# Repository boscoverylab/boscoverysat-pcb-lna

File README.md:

# Proyecto BoscoverySAT

### Descripción.

Este repositorio contiene el esquema electrónico así como el diseño de placa PCB para la implementación de un preamplificador LNB.

### Contenido del repositorio.

El presente repositorio está dividido en los siguientes directorios:

* [eagle](eagle/) - Contiene el proyecto donde se ha diseñado el esquema de circuito y se ha creado el PCB.
* [docs](docs/) - Contiene información adicional del proyecto como listado de componentes o fotolito del PCB.
* img - Esta carpeta contiene imágenes propias de la configuración del repositorio.

### Características del diseño.

El proyecto de esquema y placa PCB ha sido realizado mediante la aplicación [Cadsoft Eagle 6.5.0](http://www.cadsoftusa.com/download-eagle/).

### Contacto.

Para cualquier duda o contacto que desee realizar, por favor, remita un correo electrónico a la siguiente dirección: [boscoverylab@gmail.com](boscoverylab@gmail.com) y nos pondremos en contacto con usted a la mayor brevedad.

Si lo desea, también puede contactar con nosotros a través de nuestra cuenta de Twitter [@boscoverylab](https://www.twitter.com/boscoverylab).

### Licenciamiento.

Cualquier producto, marca comercial o nombre corporativo empleado en el contenido del presente repositorio, se ha usado con el objetivo de identificar y/o explicar conceptos, sin intención alguna de infringir los términos de uso y/o licencias de los mismos.

El presente documento se distribuye en cualquiera de sus formatos, bajo la licencia internacional [Reconocimiento-NoComercial-CompartirIgual 4.0 Internacional de Creative Commons](http://creativecommons.org/licenses/by-nc-sa/4.0/), no estando autorizada la reclamación de ningún derecho ni cantidad económica alguna en nombre de su autor o autores, a ninguna Entidad de Derechos de Autor, tanto española como internacional.

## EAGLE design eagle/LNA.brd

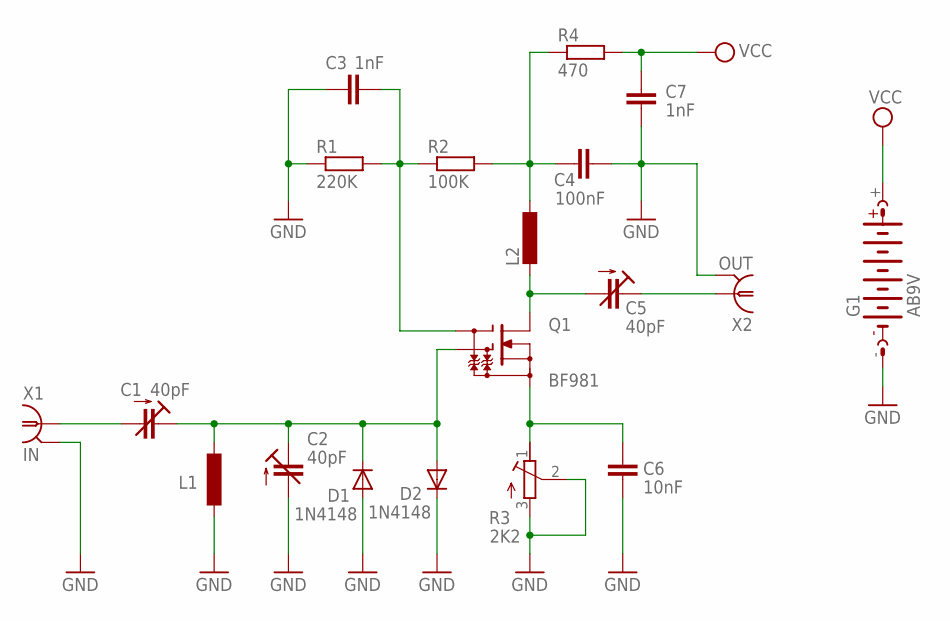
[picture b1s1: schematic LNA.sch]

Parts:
C1, C2, C5: 40pF; CTRIM808-BC
C3, C7: 1nF; C050-025X075
C4: 100nF; C050-025X075
C6: 10nF; C050-025X075
D1, D2: 1N4148; DO35-7
G1: AB9V
L1, L2: L-EU0204/5; 0204/5
Q1: BF981; SOT103
R1: 220K; 0207/10
R2: 100K; 0207/10
R3: 2K2; RTRIM43P
R4: 470; 0207/10
X1: IN; A1944
X2: OUT; A1944

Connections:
GND: C2.2 (A), C3.1, C4.2, C6.2, C7.2, D1.A, D2.C, G1.-, L1.2, R1.1, R3.2 (S), R3.3 (E), X1.2, X1.3 (2), X1.4 (2), X1.5 (2), X2.2, X2.3 (2), X2.4 (2), X2.5 (2)
unnamed: C4.1, L2.1, R2.2, R4.1
unnamed: C3.2, Q1.4-G1 (G1), R1.2, R2.1
unnamed: C1.1 (E), C2.1 (E), D1.C, D2.A, L1.1, Q1.3-G2 (G2)
unnamed: C5.2 (A), L2.2, Q1.2-D (DRAIN)
unnamed: C5.1 (E), X2.1
unnamed: C1.2 (A), X1.1
unnamed: C6.1, Q1.1-S (SOURCE), R3.1 (A)
VCC: C7.1, G1.+, R4.2

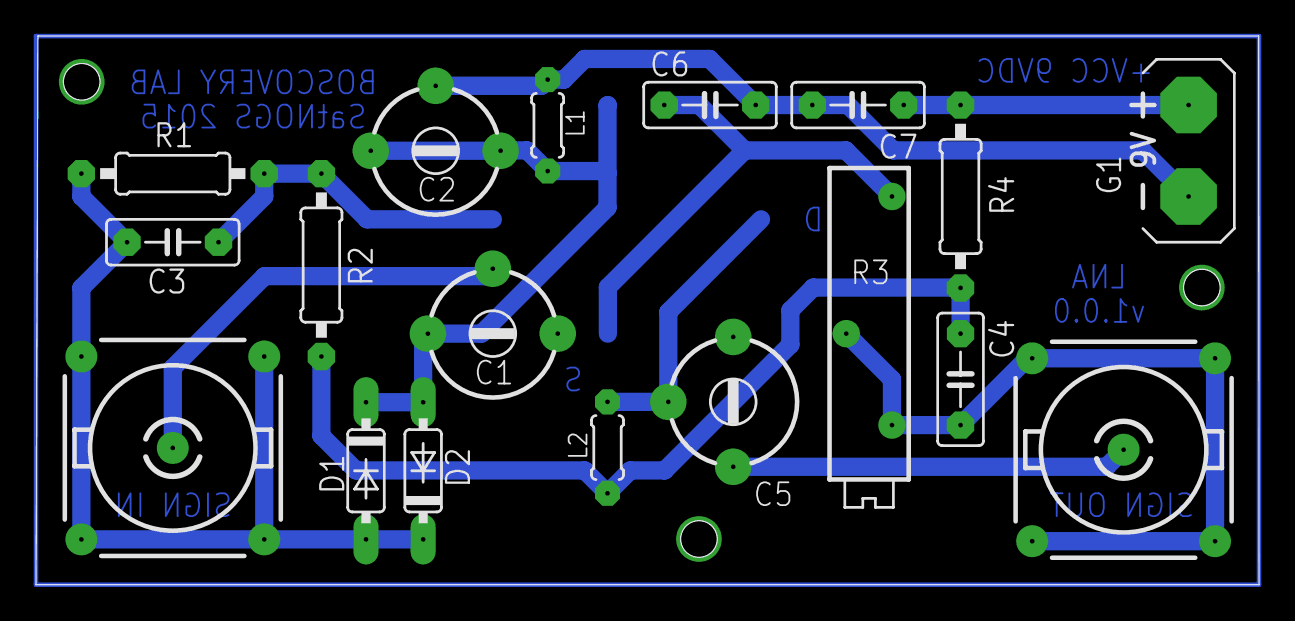
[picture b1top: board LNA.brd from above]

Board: 2 copper layers, 67.9 x 30.5 mm, 19 parts (1 on the bottom side), 9 nets.

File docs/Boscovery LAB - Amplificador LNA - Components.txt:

Partlist

Exported from LNA.sch at 30/05/2015 3:09:28

EAGLE Version 6.5.0 Copyright (c) 1988-2013 CadSoft

Assembly variant: 

Part     Value          Device          Package      Library        Sheet

C1       40pF           C-TRIMM808      CTRIM808-BC  resistor       1
C2       40pF           C-TRIMM808      CTRIM808-BC  resistor       1
C3       1nF            C-EU050-025X075 C050-025X075 resistor       1
C4       100nF          C-EU050-025X075 C050-025X075 resistor       1
C5       40pF           C-TRIMM808      CTRIM808-BC  resistor       1
C6       10nF           C-EU050-025X075 C050-025X075 resistor       1
C7       1nF            C-EU050-025X075 C050-025X075 resistor       1
D1       1N4148         1N4148DO35-7    DO35-7       diode          1
D2       1N4148         1N4148DO35-7    DO35-7       diode          1
G1       AB9V           AB9V            AB9V         battery        1
L1                      L-EU0204/5      0204/5       resistor       1
L2                      L-EU0204/5      0204/5       resistor       1
Q1       BF981          BF981           SOT103       transistor-fet 1
R1       220K           R-EU_0207/10    0207/10      resistor       1
R2       100K           R-EU_0207/10    0207/10      resistor       1
R3       2K2            R-TRIMM43P      RTRIM43P     resistor       1
R4       470            R-EU_0207/10    0207/10      resistor       1
X1       IN             A1944-50        A1944        con-coax       1
X2       OUT            A1944-50        A1944        con-coax       1

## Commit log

2015-06-02 LNA preamplifier electronics schema and PCB layout added to the repository.

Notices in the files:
README.md:
Licencia Creative Commons 4.0
